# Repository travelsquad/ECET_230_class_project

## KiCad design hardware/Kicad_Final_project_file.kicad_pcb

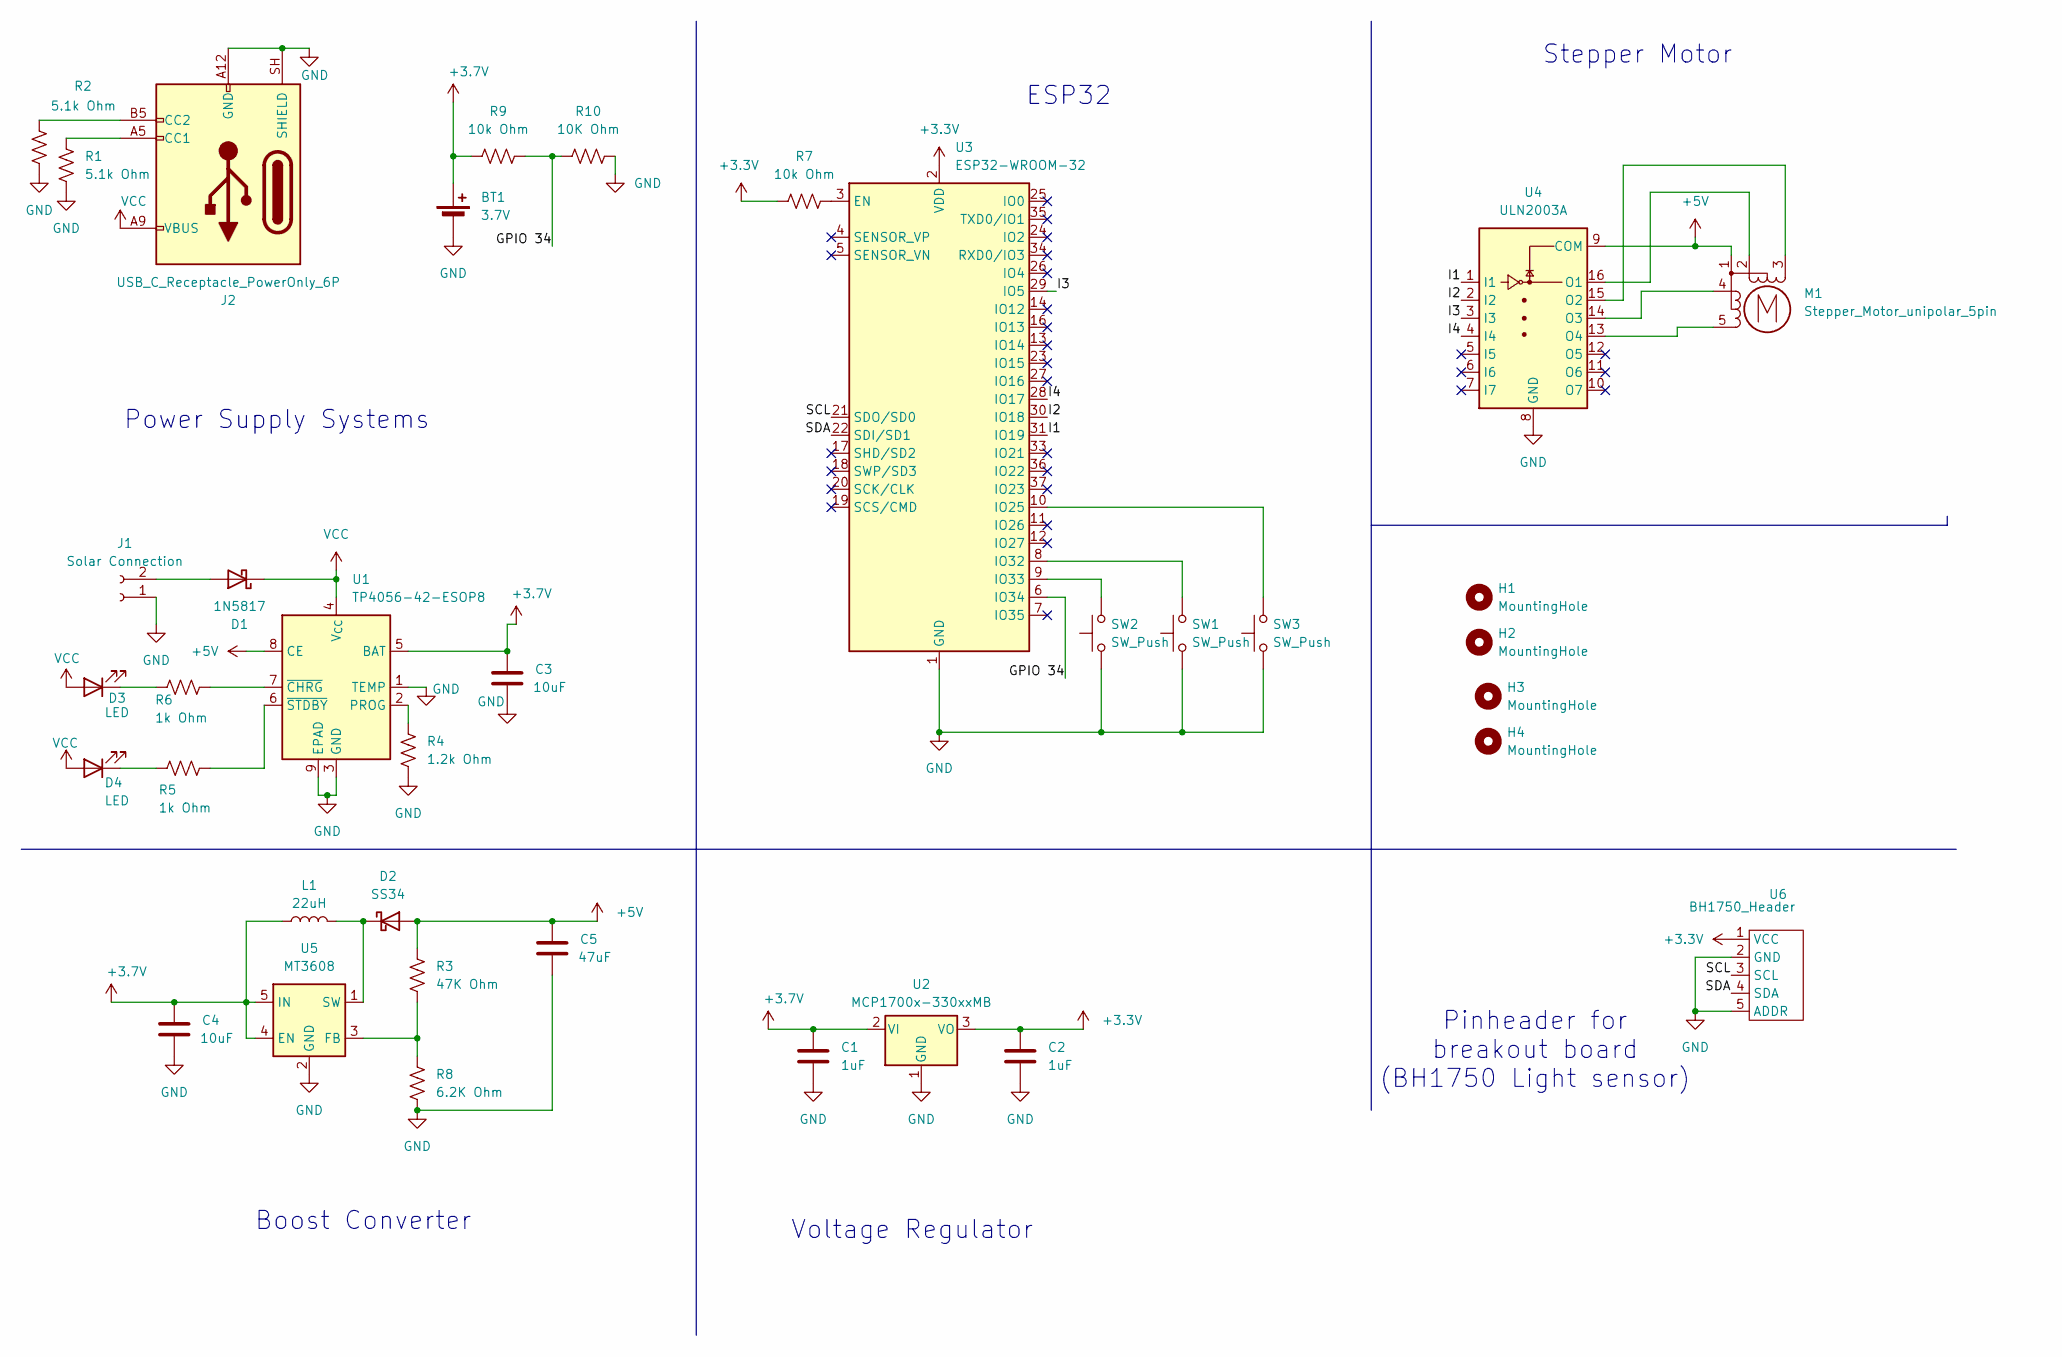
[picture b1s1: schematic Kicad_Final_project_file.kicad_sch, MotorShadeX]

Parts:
BT1: 3.7V; BatteryHolder_TruPower_BH-331P_3xAA
C1, C2: 1uF; CP_Elec_3x5.3
C3, C4: 10uF; CP_Elec_3x5.3
C5: 47uF; CP_Elec_3x5.3
D1: 1N5817; D_DO-41_SOD81_P10.16mm_Horizontal
D2: SS34; D_SMA
D3, D4: LED; LED_0805_2012Metric
H1, H2, H3, H4: MountingHole; MountingHole_2.1mm
J1: Solar Connection; JST_EH_B2B-EH-A_1x02_P2.50mm_Vertical
J2: USB_C_Receptacle_PowerOnly_6P; USB_C_Receptacle_GCT_USB4125-xx-x_6P_TopMnt_Horizontal
L1: 22uH; L_12x12mm_H4.5mm
M1: Stepper_Motor_unipolar_5pin; JST_XH_B5B-XH-A_1x05_P2.50mm_Vertical
R1, R2: 5.1k Ohm; R_0805_2012Metric
R3: 47K Ohm; R_0805_2012Metric
R4: 1.2k Ohm; R_0805_2012Metric
R5, R6: 1k Ohm; R_0805_2012Metric
R7, R9: 10k Ohm; R_0805_2012Metric
R8: 6.2K Ohm; R_0805_2012Metric
R10: 10K Ohm; R_0805_2012Metric
SW1, SW2, SW3: SW_Push; Nidec_Copal_CAS-120A
U1: TP4056-42-ESOP8; SOIC-8-1EP_3.9x4.9mm_P1.27mm_EP2.41x3.3mm_ThermalVias
U2: MCP1700x-330xxMB; SOT-89-3
U3: ESP32-WROOM-32
U4: ULN2003A; DIP-16_W10.16mm_LongPads
U5: MT3608; SOT-23-6
U6: BH1750_Header; PinHeader_1x05_P2.54mm_Vertical

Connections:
+3.3V: C2.1, R7.1, U2.3 (VO), U3.2 (VDD), U6.1 (VCC)
+3.7V: BT1.1 (+), C1.1, C3.1, C4.1, L1.1, R9.1, U1.5 (BAT), U2.2 (VI), U5.4 (EN), U5.5 (IN)
+5V: C5.1, D2.2 (A), M1.1, R3.1, U1.8 (CE), U4.9 (COM)
/GPIO 34: R9.2, R10.1, U3.6 (IO34)
/GPIO_36: U3.4 (SENSOR_VP)
/I1: U3.31 (IO19), U4.1 (I1)
/I2: U3.30 (IO18), U4.2 (I2)
/I3: U3.29 (IO5), U4.3 (I3)
/I4: U3.28 (IO17), U4.4 (I4)
/SCL: U3.21 (SDO/SD0), U6.3 (SCL)
/SDA: U3.22 (SDI/SD1), U6.4 (SDA)
GND: BT1.2 (-), C1.2, C2.2, C3.2, C4.2, C5.2, J1.1, J2.A12 (GND), J2.B12 (GND), J2.SH (SHIELD), R1.2, R2.2, R4.2, R8.2, R10.2, SW1.1, SW2.1, SW3.1, U1.1 (TEMP), U1.3 (GND), U1.9 (EPAD), U2.1 (GND), U3.1 (GND), U3.15 (GND), U3.38 (GND), U3.39 (GND), U4.8 (GND), U5.2 (GND), U6.2 (GND), U6.5 (ADDR)
unnamed: D1.2 (A), J1.2
unnamed: D2.1 (K), L1.2, U5.1 (SW)
unnamed: D3.1 (K), R6.2
unnamed: D4.1 (K), R5.2
unnamed: J2.A5 (CC1), R1.1
unnamed: J2.B5 (CC2), R2.1
unnamed: M1.3 (-_3), U4.15 (O2)
unnamed: R4.1, U1.2 (PROG)
unnamed: R6.1, U1.7 (~CHRG)
unnamed: R5.1, U1.6 (~STDBY)
unnamed: R7.2, U3.3 (EN)
unnamed: SW3.2, U3.10 (IO25)
unnamed: SW1.2, U3.8 (IO32)
unnamed: SW2.2, U3.9 (IO33)
unnamed: M1.2, U4.16 (O1)
unnamed: M1.4, U4.14 (O3)
unnamed: M1.5, U4.13 (O4)
unnamed: R3.2, R8.1, U5.3 (FB)
VCC: D1.1 (K), D3.2 (A), D4.2 (A), J2.A9 (VBUS), J2.B9 (VBUS), U1.4 (V_{CC})

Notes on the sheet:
Pinheader for breakout board (BH1750 Light sensor)
Stepper Motor
Boost Converter
Power Supply Systems
Voltage Regulator
ESP32

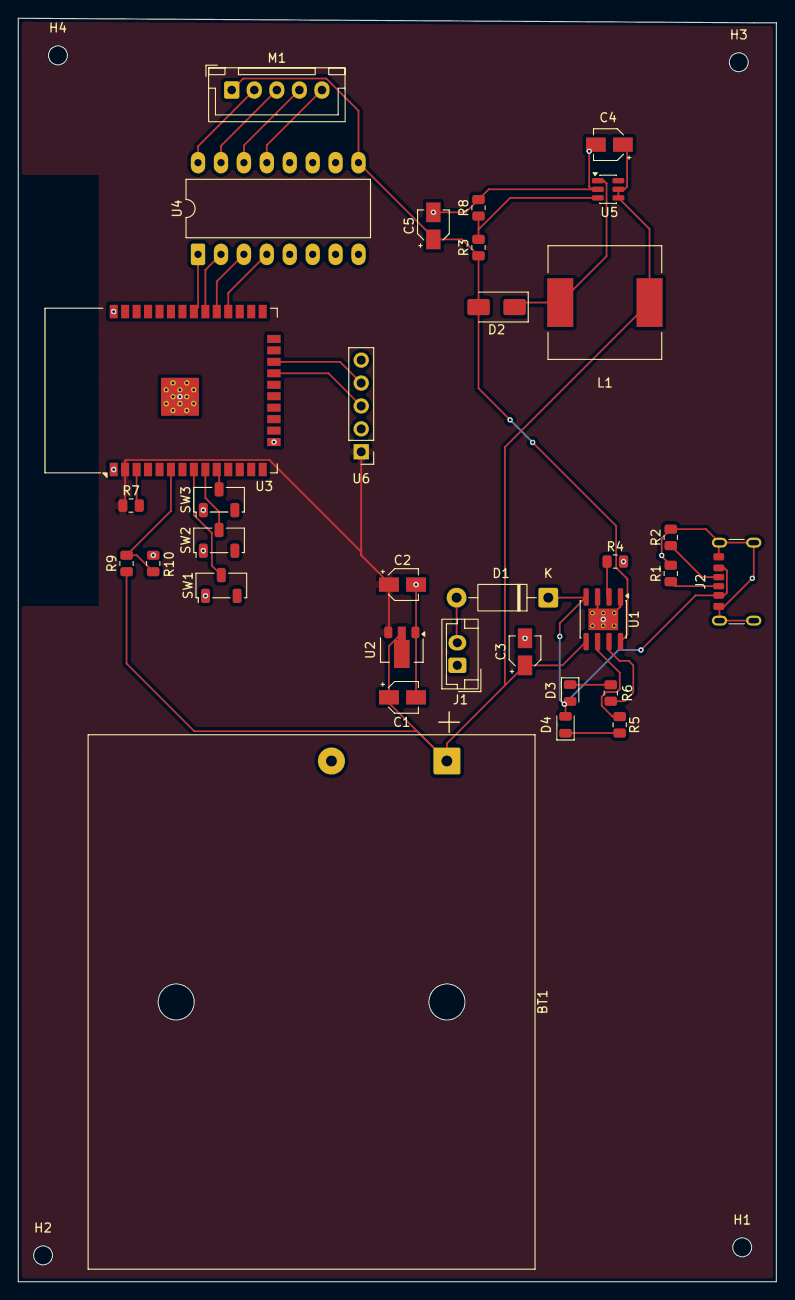
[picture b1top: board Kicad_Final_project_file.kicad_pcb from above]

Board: 2 copper layers, 84.0 x 140.0 mm, 37 parts (0 on the bottom side), 30 nets.

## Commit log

2026-02-11 first upload
2026-02-11 code files and wiring plan
2026-02-11 Create GoodnotesNotebook
2026-02-11 Update GoodnotesNotebook
    added link
